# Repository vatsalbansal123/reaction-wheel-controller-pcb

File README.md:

# Reaction Wheel BLDC Motor Control PCB

A compact, single-board controller for a brushless DC (BLDC) reaction wheel.

### Board at a glance

| | |
|---|---|
| **MCU** | STM32G431CBTx (Cortex-M4F, LQFP-48) |
| **Gate driver** | DRV8311H three-phase BLDC driver |
| **Communication** | CAN (SN65HVD231) + USB 2.0 (USB-C) |
| **Power input** | USB-C 5 V and screw-terminal motor supply |
| **Layers** | 2-layer copper (F.Cu / B.Cu) |
| **Outline** | ~48.6 × 49.5 mm, rounded corners (R2.5), four M2 corner mounting holes (H1–H4) |
| **Designed with** | KiCad 10 |

## Schematic

## PCB

| Top | Bottom |
|-----|--------|
|  |  |

## Key Components

| Reference | Part | Function |
|-----------|------|----------|
| U2 | STM32G431CBTx | Cortex-M4 motor-control MCU (LQFP-48) |
| U4 | DRV8311H | Three-phase BLDC gate driver / motor driver |
| U3 | AS5047D | Magnetic rotary position (angle) sensor |
| U5 | SN65HVD231 | CAN transceiver |
| U6 | TPS562200 | Step-down (buck) converter |
| U1 | USBLC6-2SC6 | USB ESD protection |
| D3 | NUP2105L | CAN bus ESD protection |
| Y1 | 16 MHz crystal | MCU clock source |
| J4 | USB-C receptacle | Power + USB 2.0 data |
| MT1 | Phoenix screw terminal | Motor power input |

### Connectors & I/O

- **J4** — USB-C (USB 2.0 + power)
- **MT1** — 2-pin screw terminal (motor phases / power)
- **J1** — 1x4 header, CAN (CAN_H / CAN_L)
- **J5** — 1x4 header, I²C (SDA / SCL)
- **J2** — 1x4 header, SWD debug (CLK / IO)
- **J6** — 1x6 header, SPI (CS / SCK / MISO / MOSI)
- **J3** — 1x3 pin header
- **SW1** — SPST tactile button

### Passives & Discretes

- **Capacitors:** 10n, 10p, 100n, 0.1u, 1u, 4.7u, 10u, 22u (0805 SMD)
- **Inductors:** 2.2u (0402), 120R ferrite bead (FB1)
- **Resistors:** 5k1, 10k, 30.1k, 47k, 100k (0402 / 0603 SMD)
- **Diodes:** SS34 Schottky (D1, D2)

> A full bill of materials can be regenerated from the schematic with:
> ```
> kicad-cli sch export bom reaction-wheel-bldc-motor-control-pcb.kicad_sch -o bom.csv
> ```

## Design Files

- `reaction-wheel-bldc-motor-control-pcb.kicad_sch` — schematic
- `reaction-wheel-bldc-motor-control-pcb.kicad_pcb` — PCB layout
- `reaction-wheel-bldc-motor-control-pcb.kicad_pro` — KiCad project

Designed with **KiCad 10**.

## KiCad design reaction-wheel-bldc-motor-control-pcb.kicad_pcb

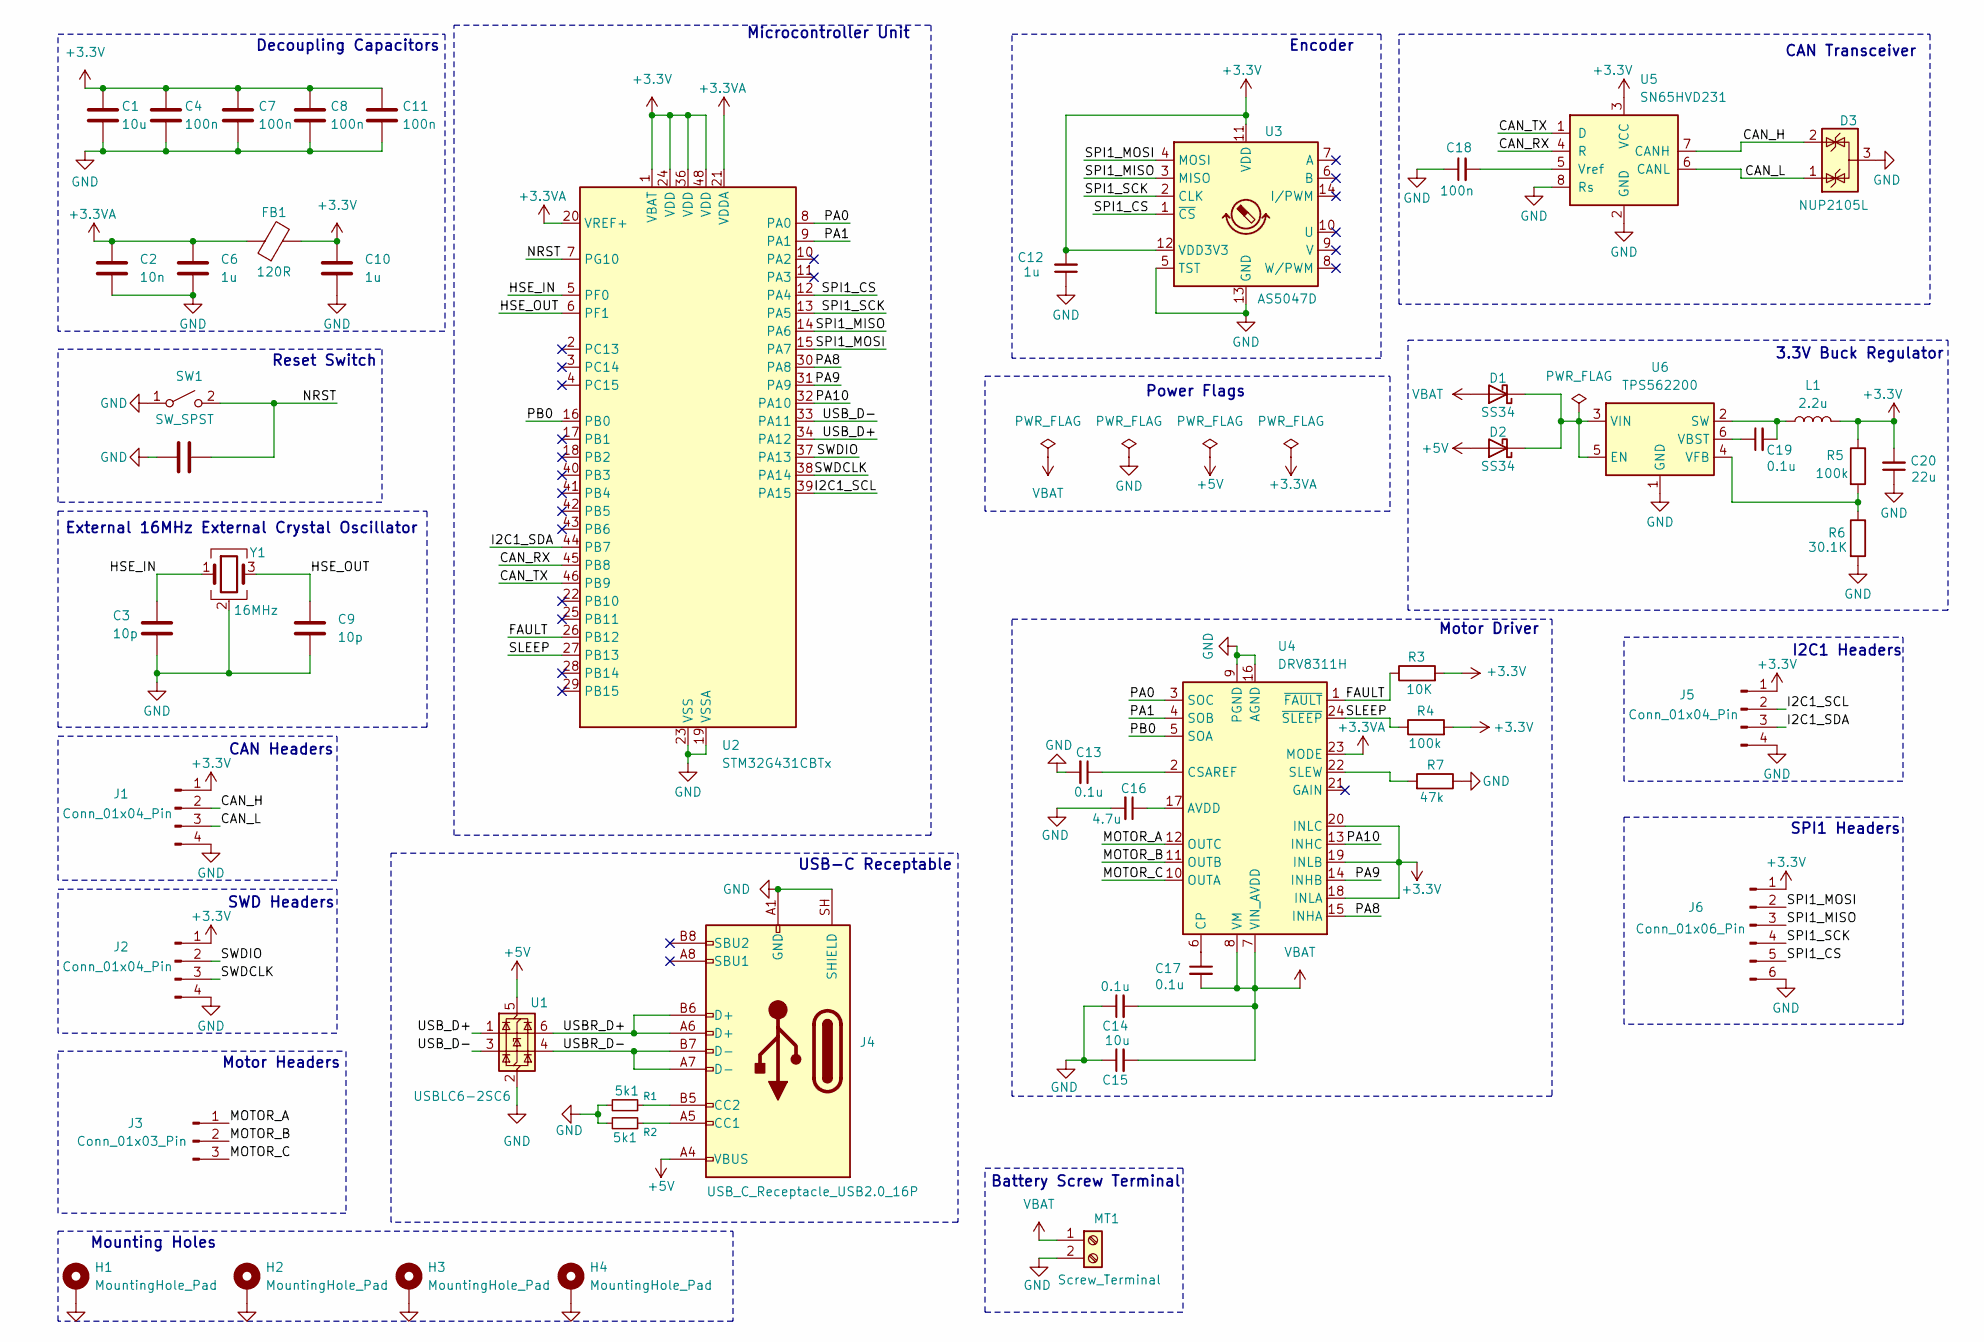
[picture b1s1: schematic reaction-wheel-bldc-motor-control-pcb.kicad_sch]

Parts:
C1, C15: 10u; C_0805_2012Metric
C2: 10n; C_0805_2012Metric
C3, C9: 10p; C_0805_2012Metric
C4, C7, C8, C11, C18: 100n; C_0805_2012Metric
C5, C13, C14, C17, C19: 0.1u; C_0805_2012Metric
C6, C10, C12: 1u; C_0805_2012Metric
C16: 4.7u; C_0805_2012Metric
C20: 22u; C_0805_2012Metric
D1, D2: SS34; D_SMA
D3: NUP2105L; SOT-23
FB1: 120R; L_0603_1608Metric
H1, H2, H3, H4: MountingHole_Pad; MountingHole_2.2mm_M2_Pad
J1, J2, J5: Conn_01x04_Pin; PinHeader_1x04_P2.54mm_Vertical
J3: Conn_01x03_Pin; PinHeader_1x03_P2.54mm_Vertical
J4: USB_C_Receptacle_USB2.0_16P; USB_C_Receptacle_G-Switch_GT-USB-7010ASV
J6: Conn_01x06_Pin; PinHeader_1x06_P2.54mm_Vertical
L1: 2.2u; L_0402_1005Metric
MT1: Screw_Terminal; TerminalBlock_Phoenix_MKDS-1,5-2-5.08_1x02_P5.08mm_Horizont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
R1, R2: 5k1; R_0402_1005Metric
R3: 10K; R_0402_1005Metric
R4, R5: 100k; R_0603_1608Metric
R6: 30.1K; R_0603_1608Metric
R7: 47k; R_0603_1608Metric
SW1: SW_SPST; SW_SPST_SKQG_WithStem
U1: USBLC6-2SC6; SOT-23-6
U2: STM32G431CBTx; LQFP-48_7x7mm_P0.5mm
U3: AS5047D; TSSOP-14_4.4x5mm_P0.65mm
U4: DRV8311H; Texas_RRW0024A_WQFN-24-1EP_3x3mm_P0.4mm_EP1.9x1.9mm
U5: SN65HVD231; SOIC-8_3.9x4.9mm_P1.27mm
U6: TPS562200; SOT-23-6
Y1: 16MHz; Crystal_SMD_3225-4Pin_3.2x2.5mm

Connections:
+3.3V: C1.1, C4.1, C7.1, C8.1, C10.1, C11.1, C12.2, C20.2, FB1.2, J1.1, J2.1, J5.1, J6.1, L1.2, R3.2, R4.2, R5.1, U2.1 (VBAT), U2.24 (VDD), U2.36 (VDD), U2.48 (VDD), U3.11 (VDD), U3.12 (VDD3V3), U4.18 (INLA), U4.19 (INLB), U4.20 (INLC), U5.3 (VCC)
+3.3VA: C2.1, C6.1, FB1.1, U2.20 (VREF+), U2.21 (VDDA), U4.23 (MODE)
+5V: D2.2 (A), J4.A4 (VBUS), J4.A9 (VBUS), J4.B4 (VBUS), J4.B9 (VBUS), U1.5 (VBUS)
/CAN_H: D3.2 (K), J1.2, U5.7 (CANH)
/CAN_L: D3.1 (K), J1.3, U5.6 (CANL)
/CAN_RX: U2.45 (PB8), U5.4 (R)
/CAN_TX: U2.46 (PB9), U5.1 (D)
/FAULT: R3.1, U2.26 (PB12), U4.1 (~FAULT)
/HSE_IN: C3.1, U2.5 (PF0), Y1.1
/HSE_OUT: C9.1, U2.6 (PF1), Y1.3
/I2C1_SCL: J5.2, U2.39 (PA15)
/I2C1_SDA: J5.3, U2.44 (PB7)
/MOTOR_A: J3.1, U4.12 (OUTC)
/MOTOR_B: J3.2, U4.11 (OUTB)
/MOTOR_C: J3.3, U4.10 (OUTA)
/NRST: C5.2, SW1.2 (B), U2.7 (PG10)
/PA0: U2.8 (PA0), U4.3 (SOC)
/PA1: U2.9 (PA1), U4.4 (SOB)
/PA8: U2.30 (PA8), U4.15 (INHA)
/PA9: U2.31 (PA9), U4.14 (INHB)
/PA10: U2.32 (PA10), U4.13 (INHC)
/PB0: U2.16 (PB0), U4.5 (SOA)
/SLEEP: R4.1, U2.27 (PB13), U4.24 (~SLEEP)
/SPI1_CS: J6.5, U2.12 (PA4), U3.1 (~CS)
/SPI1_MISO: J6.3, U2.14 (PA6), U3.3 (MISO)
/SPI1_MOSI: J6.2, U2.15 (PA7), U3.4 (MOSI)
/SPI1_SCK: J6.4, U2.13 (PA5), U3.2 (CLK)
/SWDCLK: J2.3, U2.38 (PA14)
/SWDIO: J2.2, U2.37 (PA13)
/USBR_D+: J4.A6 (D+), J4.B6 (D+), U1.6 (I/O1)
/USBR_D-: J4.A7 (D-), J4.B7 (D-), U1.4 (I/O2)
/USB_D+: U1.1 (I/O1), U2.34 (PA12)
/USB_D-: U1.3 (I/O2), U2.33 (PA11)
GND: C1.2, C2.2, C3.2, C4.2, C5.1, C6.2, C7.2, C8.2, C9.2, C10.2, C11.2, C12.1, C13.2, C14.1, C15.1, C16.2, C18.1, C20.1, D3.3 (A), H1.1 (1_1), H2.1 (1_1), H3.1 (1_1), H4.1 (1_1), J1.4, J2.4, J4.A1 (GND), J4.A12 (GND), J4.B1 (GND), J4.B12 (GND), J4.SH (SHIELD), J5.4, J6.6, MT1.2, R1.2, R2.2, R6.2, R7.1, SW1.1 (A), U1.2 (GND), U2.19 (VSSA), U2.23 (VSS), U2.35 (VSS), U2.47 (VSS), U3.5 (TST), U3.13 (GND), U4.9 (PGND), U4.16 (AGND), U4.25 (PGND), U5.2 (GND), U5.8 (Rs), U6.1 (GND), Y1.2 (G), Y1.4 (G)
unnamed: D1.1 (K), D2.1 (K), U6.3 (VIN), U6.5 (EN)
unnamed: J4.A5 (CC1), R2.1
unnamed: J4.B5 (CC2), R1.1
unnamed: C16.1, U4.17 (AVDD)
unnamed: C17.1, U4.6 (CP)
unnamed: C13.1, U4.2 (CSAREF)
unnamed: R7.2, U4.22 (SLEW)
unnamed: C18.2, U5.5 (Vref)
unnamed: C19.2, L1.1, U6.2 (SW)
unnamed: C19.1, U6.6 (VBST)
unnamed: R5.2, R6.1, U6.4 (VFB)
VBAT: C14.2, C15.2, C17.2, D1.2 (A), MT1.1, U4.7 (VIN_AVDD), U4.8 (VM)

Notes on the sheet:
Microcontroller Unit
Power Flags
Motor Headers
Motor Driver
SPI1 Headers
External 16MHz External Crystal Oscillator
I2C1 Headers
Mounting Holes
Encoder
Reset Switch
Battery Screw Terminal
CAN Transceiver
SWD Headers
3.3V Buck Regulator
USB-C Receptable
CAN Headers
Decoupling Capacitors

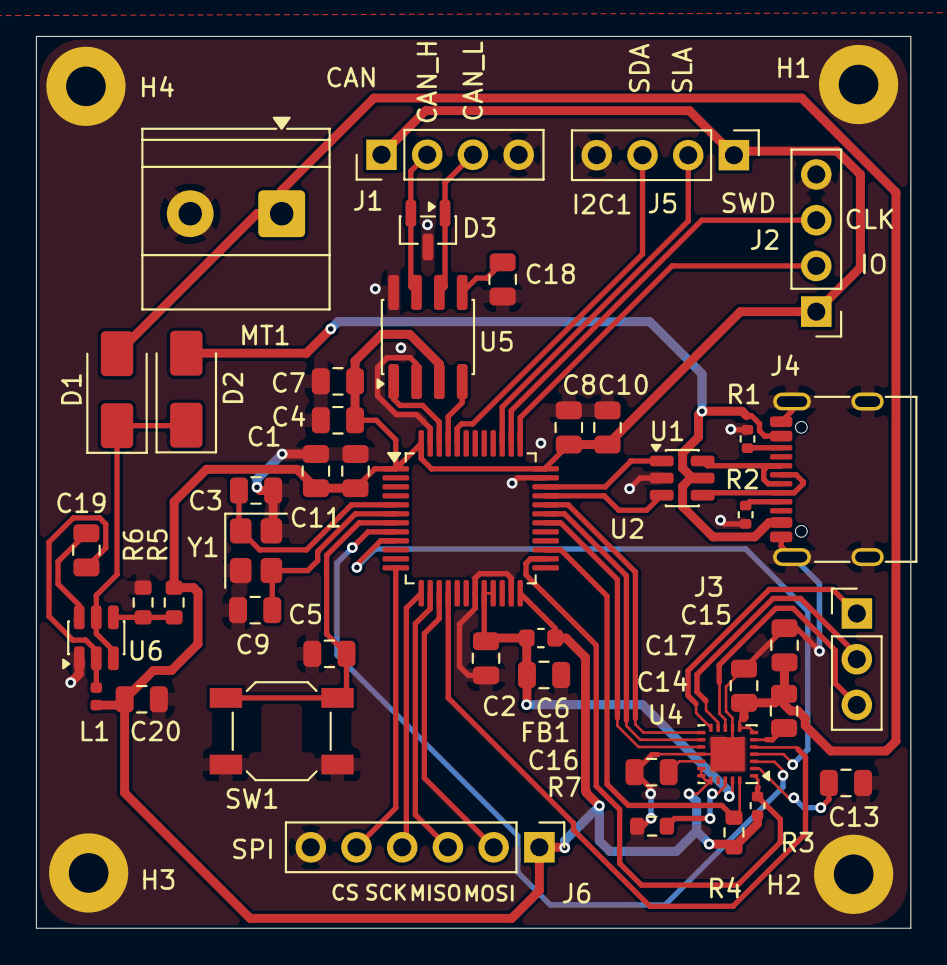
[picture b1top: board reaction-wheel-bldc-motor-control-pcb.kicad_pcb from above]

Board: 2 copper layers, 48.6 x 49.5 mm, 49 parts (0 on the bottom side), 46 nets.

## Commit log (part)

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2026-06-18 schematic almost complete
2026-06-23 started with pcb routing
2026-06-26 routing almost finished
2026-06-29 fixed unrouted connections
